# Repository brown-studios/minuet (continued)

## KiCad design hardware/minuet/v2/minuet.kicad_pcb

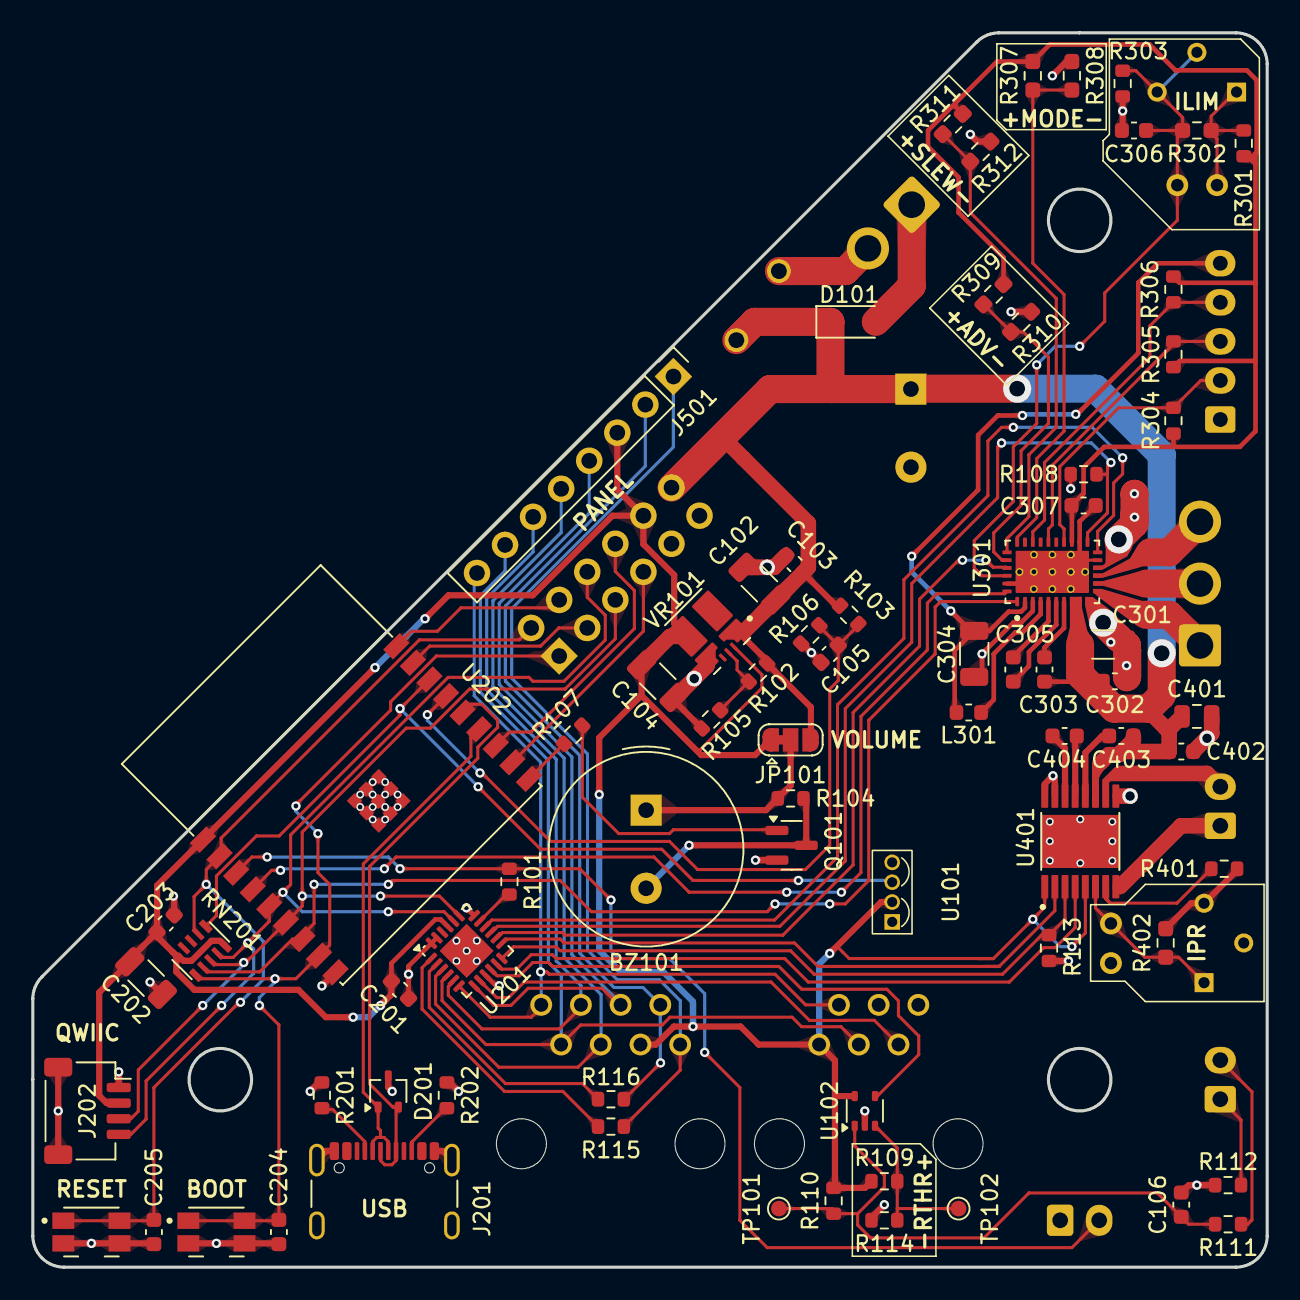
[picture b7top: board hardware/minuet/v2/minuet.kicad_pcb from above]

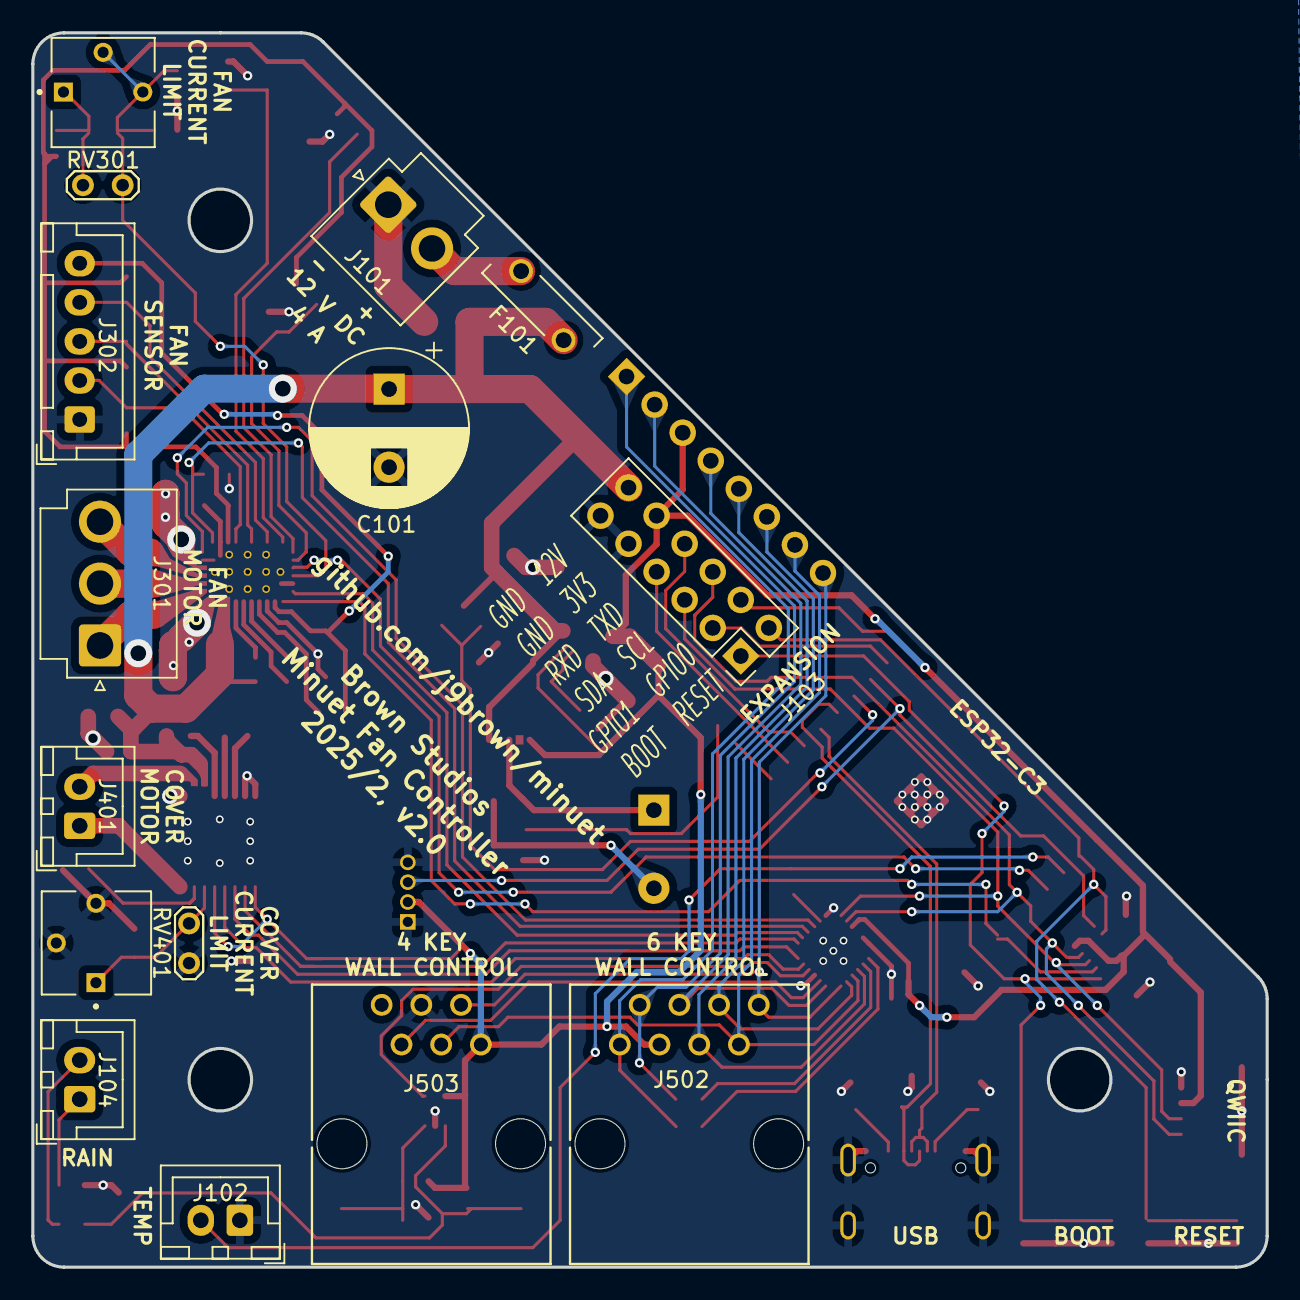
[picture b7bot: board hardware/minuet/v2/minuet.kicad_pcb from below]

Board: 2 copper layers, 79.0 x 79.0 mm, 93 parts (15 on the bottom side), 76 nets.

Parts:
BZ101: PS1240P02BT; Buzzer_TDK_PS1240P02BT_D12.2mm_H6.5mm
C101: 1000u; CP_Radial_D10.0mm_P5.00mm
C102, C202, C301: 10u; C_1206_3216Metric
C103, C106, C201, C203, C302, C306, C402, C403: 100n; C_0603_1608Metric
C104, C304: 22u; C_1206_3216Metric
C105, C205, C303, C307: 1u; C_0603_1608Metric
C204: 10p; C_0603_1608Metric
C305: 47n; C_0603_1608Metric
C401: 2.2u; C_0805_2012Metric
C404: 22n; C_0603_1608Metric
D101: SMF16A-E3-08; D_SMF
D201: DF3A5.6LFU; SOT-323_SC-70
F101: RGEF400K-2; RGEF400K
J101: B2P-VH-B; JST_VH_B2P-VH-B_1x02_P3.96mm_Vertical
J102, J104, J401: B2B-XH-A; JST_XH_B2B-XH-A_1x02_P2.50mm_Vertical
J103: PPPC062LFBN-RC; PinSocket_2x06_P2.54mm_Vertical
J201: USB4105-GF-A; USB_C_Receptacle_GCT_USB4105-xx-A_16P_TopMnt_Horizontal
J202: SM04B-SRSS-TB; JST_SH_SM04B-SRSS-TB_1x04-1MP_P1.00mm_Horizontal
J301: B3P-VH-B; JST_VH_B3P-VH-B_1x03_P3.96mm_Vertical
J302: B5B-XH-A; JST_XH_B5B-XH-A_1x05_P2.50mm_Vertical
J501: G800LE300018YEU; PinHeader_1x08_P2.54mm_Vertical
J502: MTJ-889X1; CONN_MTJ-889X1_ADM
J503: MTJ-669X1; CONN_MTJ-669X1_ADM
JP101: SolderJumper_3_Bridged12; SolderJumper-3_P1.3mm_Bridged12_RoundedPad1.0x1.5mm
L301: 22u; L_0603_1608Metric
NT101, NT401: NetTie_2; NetTie-2_SMD_Pad1.0mm
NT102, NT402: NetTie_2; NetTie-2_SMD_Pad0.2mm
Q101: MMBT3904; SOT-23
R101, R106, R107, R108, R113, R115, R116, R301, R303: 10K; R_0603_1608Metric
R102, R401: 62K; R_0603_1608Metric
R103, R109, R110, R111, R112: 100K; R_0603_1608Metric
R104: 1K; R_0603_1608Metric
R105: 22K; R_0603_1608Metric
R114: 1.5M; R_0603_1608Metric
R201, R202: 5.1K; R_0603_1608Metric
R302: 3.40K; R_0603_1608Metric_Pad0.98x0.95mm_HandSolder
R304, R305, R306: 4.7K; R_0603_1608Metric
R307, R309, R310, R311, R312: 0R; R_0603_1608Metric_Pad0.98x0.95mm_HandSolder
R308: 22K; R_0603_1608Metric_Pad0.98x0.95mm_HandSolder
R402: 2.80K; R_0603_1608Metric_Pad0.98x0.95mm_HandSolder
RN201: 746X101103JP; RESCAXS64P320X160X70-10N
RV301, RV401: 5K; TRIM_3362P-1-502LF
SW201, SW202: EVQ-P7A01P; SW_EVQ-P7A01P
TP101, TP102: TestPoint_Small; TestPoint_Pad_D1.0mm
TP301, TP401: TestPoint_2Pole; TestPoint_2Pads_Pitch2.54mm_Drill0.8mm
U101: TSOP39238; TSOP39238_Standoff
U102: LMV331X-SC5R; SOT-353_SC-70-5
U201: TCA9555RTWR; WQFN-24-1EP_4x4mm_P0.5mm_EP2.45x2.45mm
U202: ESP32-C3-WROOM-02
U301: MCT8315Z0HRRYR; IC_MCT8315Z0HRRYR
U401: DRV8876PWPR; IC_DRV8876PWPR
VR101: TPSM861253RDXR; VREG_TPSM861253RDXR

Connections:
+3.3V: C104.1, C201.1, C202.2, C203.1, J103.10, J202.2, J501.3, J502.3, J503.6, JP101.1 (A), NT102.2, NT402.1, R109.2, R110.1, RN201.5 (common), RN201.10 (common), U101.2 (Vs), U102.5 (V+), U201.21 (VCC), U202.1 (3V3), VR101.3 (VOUT)
+12V: C101.1, C301.1, C302.1, C303.1, D101.1 (A1), F101.2, J103.12, NT101.1, NT401.1, U301.8 (VM), U301.9 (VM)
/12V_IN: F101.1, J101.2
/12V_PWR: C102.1, C103.1, JP101.3 (B), NT101.2, R102.1, R103.2, VR101.1 (VIN)
/EN: R102.2, R105.1, VR101.6 (EN)
/RSEN: C106.1, R110.2, R111.2, TP101.1, U102.1 (+)
/RTHR: R109.1, R114.2, TP102.1, U102.3 (-)
/core/CC1: J201.A5 (CC1), R201.2
/core/CC2: J201.B5 (CC2), R202.1
/cover/CPH: C404.1, U401.13 (CPH)
/cover/CPL: C404.2, U401.14 (CPL)
/cover/IMODE: R401.2, U401.7 (IMODE)
/cover/IPROPI: R402.1, RV401.1, TP401.2, U401.6 (IPROPI)
/cover/OUT1: J401.1, U401.8 (OUT1)
/cover/OUT2: J401.2, U401.10 (OUT2)
/cover/VCP: C403.2, U401.12 (VCP)
/cover/VM: C401.2, C402.1, C403.1, NT401.2, U401.11 (VM)
/cover/VREF: NT402.2, U401.1 (EN/IN1), U401.5 (VREF)
/fan/ADVANCE: R309.2, R310.1, U301.28 (ADVANCE)
/fan/AVDD: C307.1, R301.1, R304.1, R305.1, R306.1, R307.1, R309.1, R311.1, U301.19 (AVDD)
/fan/ILIM: C306.1, R302.2, R303.1, RV301.2, RV301.3, TP301.1, U301.30 (ILIM)
/fan/MODE: R307.2, R308.1, U301.26 (MODE)
/fan/SLEW: R311.2, R312.1, U301.27 (SLEW)
/fan/U: J301.1, U301.11 (OUTA)
/fan/U_HALL: J302.2, R304.2, U301.20 (HPA)
/fan/V: J301.2, U301.12 (OUTB)
/fan/VBK: C304.1, J302.5, L301.1, U301.2 (FB_BK)
/fan/V_HALL: J302.3, R305.2, U301.22 (HPB)
/fan/W: J301.3, U301.13 (OUTC)
/fan/W_HALL: J302.4, R306.2, U301.24 (HPC)
/keypad/LED_AUTO: J501.1, J502.1, R115.2
/keypad/LED_RAIN: J501.2, J502.2, R116.2
BOOT: C204.1, J103.1, RN201.1 (R1), SW201.1_1, SW201.1_2, U202.8 (GPIO9)
GND: C101.2, C102.2, C103.2, C104.2, C105.2, C106.2, C201.2, C202.1, C203.2, C204.2, C205.2, C301.2, C302.2, C304.2, C306.2, C307.2, C401.1, C402.2, D101.2 (A2), D201.3 (A), J101.1, J102.1, J103.9, J103.11, J201.A1 (GND), J201.A12 (GND), J201.B1 (GND), J201.B12 (GND), J201.S1 (SHIELD), J202.1, J202.MP (MountPin), J302.1, J503.3, Q101.2 (E), R105.2, R106.1, R108.1, R112.2, R113.1, R114.1, R201.1, R202.2, R303.2, R308.2, R310.2, R312.2, R401.1, R402.2, RV401.2, RV401.3, SW201.2_1, SW201.2_2, SW202.2_1, SW202.2_2, TP401.1, U101.1 (GND), U101.4 (GND), U102.2 (V-), U201.9 (GND), U201.18 (A0), U201.23 (A1), U201.24 (A2), U201.25 (EPAD), U202.9 (GND), U202.19 (GND), U301.3 (GND_BK), U301.10 (PGND), U301.14 (PGND), U301.15 (DRVOFF), U301.18 (AGND), U301.31 (BRAKE), U301.33 (EP), U301.34 (EP), U301.35 (EP), U301.36 (EP), U301.37 (EP), U301.38 (EP), U301.39 (EP), U301.40 (EP), U301.41 (EP), U301.42 (EP), U301.43 (EP), U301.44 (EP), U401.9 (PGND), U401.15 (GND), U401.16 (PMODE), U401.17 (EXP), VR101.4 (PGND)
GPIO0: J103.4, U202.18 (GPIO0/ADC1_CH0/XTAL_32K_P)
GPIO1: J103.3, U202.17 (GPIO1/ADC1_CH1/XTAL_32K_N)
GPIO2_STRAP: RN201.6 (R5), U101.3 (OUT), U202.16 (GPIO2/ADC1_CH2)
GPIO3: C105.1, R103.1, R106.2, U202.15 (GPIO3/ADC1_CH3)
GPIO4: J102.2, R101.1, U202.3 (GPIO4/ADC1_CH4)
GPIO5: U202.4 (GPIO5/ADC2_CH0), U301.32 (PWM)
GPIO8_STRAP: RN201.2 (R2), U202.7 (GPIO8), U301.1 (FGOUT)
GPIO10: R107.2, U202.10 (GPIO10)
unnamed: BZ101.1 (+), JP101.2 (C), R104.1
unnamed: BZ101.2 (-), Q101.3 (C), R104.2
unnamed: J104.1, R112.1
unnamed: J104.2, R111.1
unnamed: Q101.1 (B), R107.1
unnamed: R301.2, R302.1, RV301.1, TP301.2
unnamed: C303.2, U301.7 (CP)
unnamed: C305.1, U301.6 (CPH)
unnamed: C305.2, U301.5 (CPL)
unnamed: L301.2, U301.4 (SW_BK)
unnamed: NT102.1, VR101.7 (VOS)
RESET: C205.1, J103.2, RN201.7 (R6), SW202.1_1, SW202.1_2, U202.2 (EN/CHIP_PU)
SCL: J103.6, J202.4, RN201.4 (R4), U201.20 (SDA), U202.5 (GPIO6)
SDA: J103.5, J202.3, RN201.3 (R3), U201.19 (SCL), U202.6 (GPIO7)
UART_RXD: J103.7, U202.11 (GPIO20/U0RXD)
UART_TXD: J103.8, U202.12 (GPIO21/U0TXD)
USB_D+: D201.2 (K), J201.A6 (D+), J201.B6 (D+), U202.14 (GPIO19/USB_D+)
USB_D-: D201.1 (K), J201.A7 (D-), J201.B7 (D-), U202.13 (GPIO18/USB_D-)
XIO0: R115.1, U201.1 (P00)
XIO1: R116.1, U201.2 (P01)
XIO2: J501.5, J502.5, U201.3 (P02)
XIO3: J501.7, J502.7, J503.4, U201.4 (P03)
XIO4: J501.6, J502.6, U201.5 (P04)
XIO5: J501.8, J502.8, J503.5, U201.6 (P05)
XIO6: J501.4, J502.4, U201.7 (P06)
XIO7: J503.2, U201.8 (P07)
XIO8: U102.4, U201.10
XIO9: U201.11, U401.4 (~NFAULT)
XIO10: R113.2, U201.12, U401.3 (NSLEEP)
XIO11: U201.13, U401.2 (PH/IN2)
XIO12: U201.14, U301.29 (DIR)
XIO13: R108.2, U201.15, U301.17 (~SLEEP)
XIO14: U201.16, U301.16 (~FAULT)
XIO15: R101.2, U201.17

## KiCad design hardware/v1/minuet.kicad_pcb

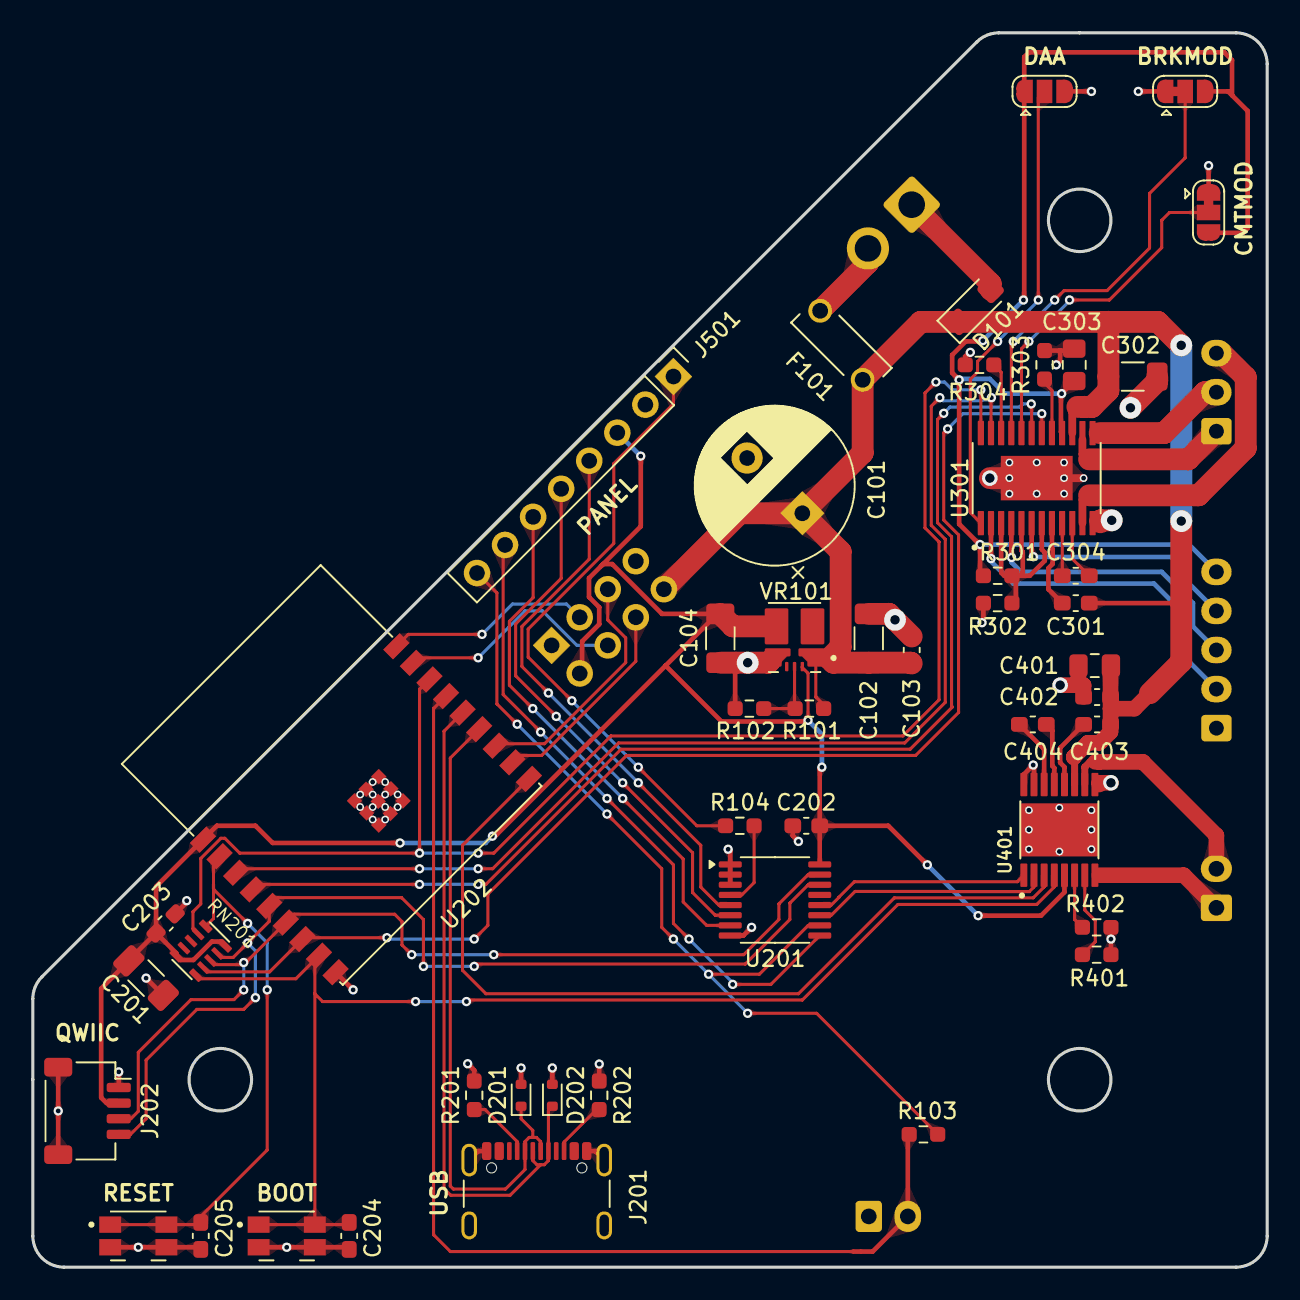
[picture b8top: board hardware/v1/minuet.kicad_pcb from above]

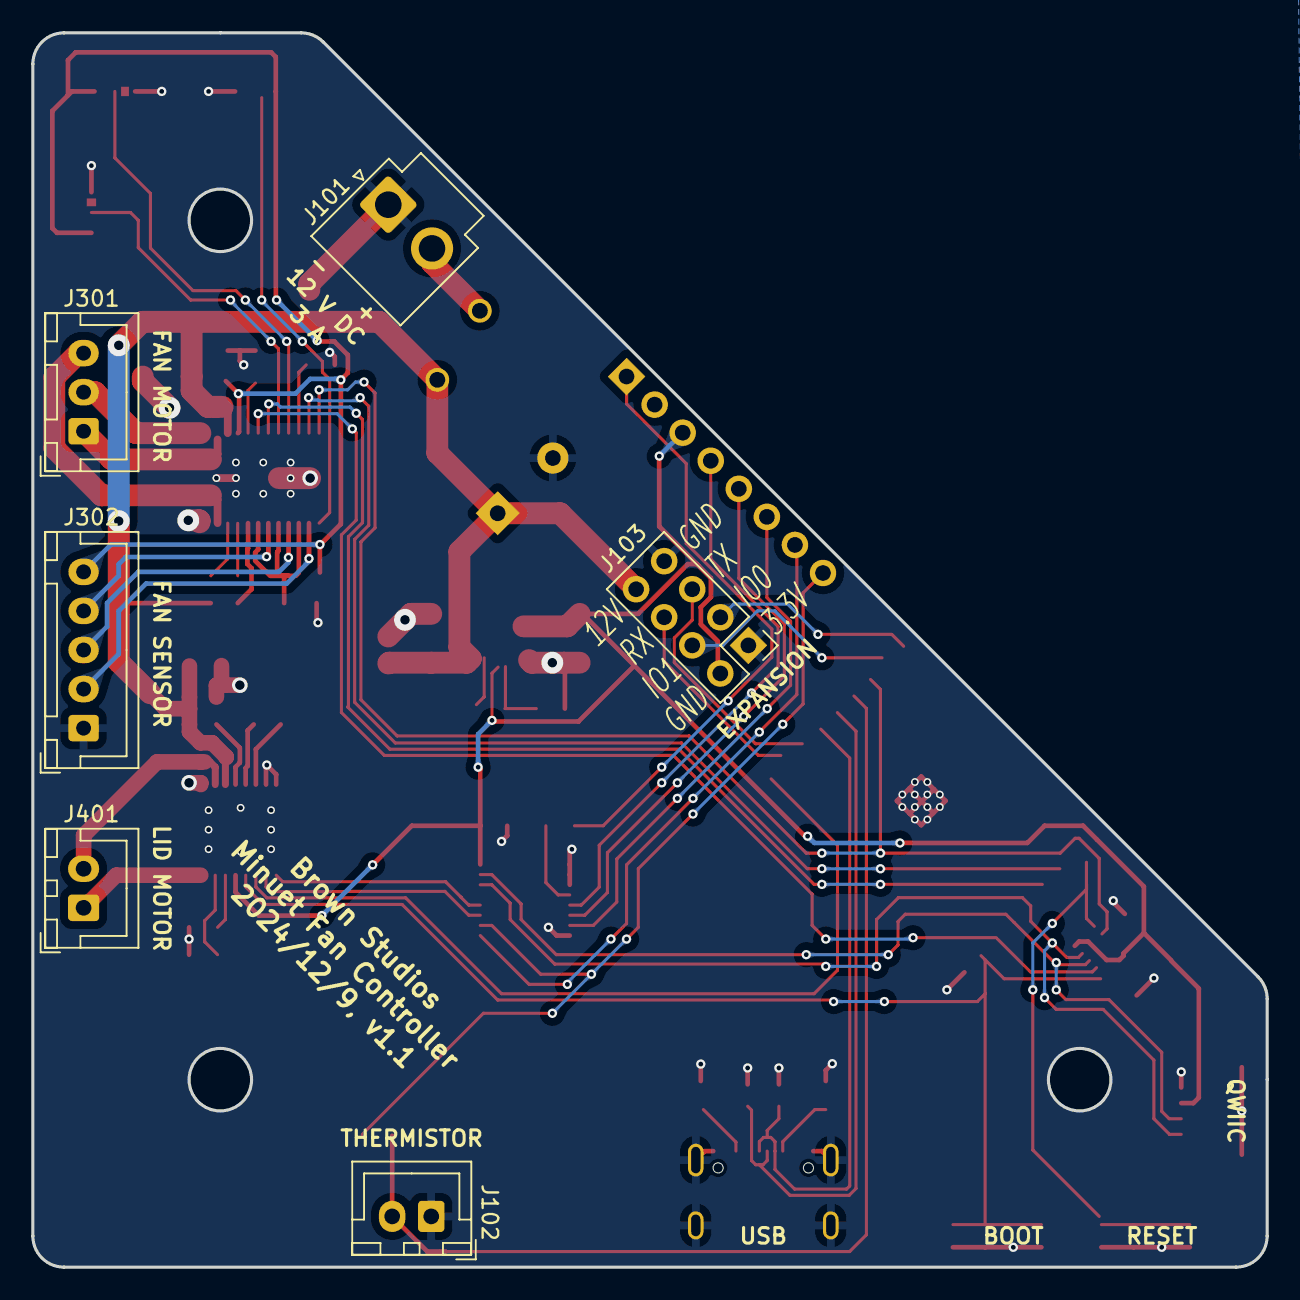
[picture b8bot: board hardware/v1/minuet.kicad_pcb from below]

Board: 2 copper layers, 79.0 x 79.0 mm, 55 parts (6 on the bottom side), 57 nets.

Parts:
C101: 680u; CP_Radial_D10.0mm_P5.00mm
C102, C201, C302: 10u; C_1206_3216Metric_Pad1.33x1.80mm_HandSolder
C103, C202, C203, C304, C402, C403: 100n; C_0603_1608Metric_Pad1.08x0.95mm_HandSolder
C104: 22u; C_1206_3216Metric_Pad1.33x1.80mm_HandSolder
C204: 10p; C_0603_1608Metric_Pad1.08x0.95mm_HandSolder
C205, C301: 1u; C_0603_1608Metric_Pad1.08x0.95mm_HandSolder
C303, C401: 2.2u; C_0805_2012Metric_Pad1.18x1.45mm_HandSolder
C404: 22n; C_0603_1608Metric_Pad1.08x0.95mm_HandSolder
D101: SMF16A-E3-08; D_SMF
D201, D202: TPD1E10B06DYAR; D_SOD-523
F101: RGEF300K-2; FUSRR505W81L660T250H1360
J101: VH_B2P-VH-B; JST_VH_B2P-VH-B_1x02_P3.96mm_Vertical
J102: B2B-XH-A_1; JST_XH_B2B-XH-A_1x02_P2.50mm_Vertical
J103: Conn_02x04; PinHeader_2x04_P2.54mm_Vertical
J201: USB4105-GF-A; USB_C_Receptacle_GCT_USB4105-xx-A_16P_TopMnt_Horizontal
J202: SM04B-SRSS-TB; JST_SH_SM04B-SRSS-TB_1x04-1MP_P1.00mm_Horizontal
J301: B3B-XH-A; JST_XH_B3B-XH-A_1x03_P2.50mm_Vertical
J302: B5B-XH-A; JST_XH_B5B-XH-A_1x05_P2.50mm_Vertical
J401: B2B-XH-A; JST_XH_B2B-XH-A_1x02_P2.50mm_Vertical
J501: Header; PinHeader_1x08_P2.54mm_Vertical
JP301, JP303: SolderJumper_3_Bridged12; SolderJumper-3_P1.3mm_Bridged12_RoundedPad1.0x1.5mm
JP302: SolderJumper_3_Open; SolderJumper-3_P1.3mm_Open_RoundedPad1.0x1.5mm
NT101: NetTie_2; NetTie-2_SMD_Pad0.3mm
NT401: NetTie_2; NetTie-2_SMD_Pad1.0mm
R101, R401: 62K; R_0603_1608Metric_Pad0.98x0.95mm_HandSolder
R102, R303: 22K; R_0603_1608Metric_Pad0.98x0.95mm_HandSolder
R103, R104, R301, R302, R304: 10K; R_0603_1608Metric_Pad0.98x0.95mm_HandSolder
R201, R202: 5.1K; R_0603_1608Metric_Pad0.98x0.95mm_HandSolder
R402: 6.8K; R_0603_1608Metric_Pad0.98x0.95mm_HandSolder
RN201: 746X101103JP; RESCAXS64P320X160X70-10N
SW201, SW202: EVQ-P7A01P; SW_EVQ-P7A01P
U201: TCA9554PWR; TSSOP-16_4.4x5mm_P0.65mm
U202: ESP32-C3-WROOM-02
U301: DRV10970PWP; SOP65P640X120-25N
U401: DRV8876PWPR; IC_DRV8876PWPR
VR101: TPSM861253RDXR; VREG_TPSM861253RDXR

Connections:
+3.3V: C104.1, C201.2, C202.1, C203.2, J103.2, J202.2, J501.3, RN201.5 (common), RN201.10 (common), U201.16 (VDD), U202.1 (3V3), U401.5 (VREF), VR101.3 (VOUT), VR101.7 (VOS)
+12V: C101.1, C102.1, C103.1, C301.2, C302.1, D101.1 (A1), F101.2, J103.8, NT401.1, R101.1, U301.15 (VM), VR101.1 (VIN)
/12V_IN: F101.1, J101.2
/EN: R101.2, R102.1, VR101.6 (EN)
/TH: J102.2, NT101.2, R103.1
/core/CC1: J201.A5 (CC1), R201.2
/core/CC2: J201.B5 (CC2), R202.1
/fan/BRKMOD: JP301.2 (C), U301.21 (BRKMOD)
/fan/CMTMOD: JP303.2 (C), U301.20 (CMTMOD)
/fan/CPN: C304.2, U301.10 (CPN)
/fan/CPP: C304.1, U301.9 (CPP)
/fan/CS: R303.2, U301.17 (CS)
/fan/DAA: JP302.2 (C), U301.1 (DAA)
/fan/RETRY: R304.2, U301.22 (RETRY)
/fan/U: J301.1, U301.14 (U)
/fan/U_HALL: J302.2, U301.2 (U_HP)
/fan/V: J301.2, U301.13 (V)
/fan/VCP: C301.1, U301.8 (VCP)
/fan/VINT: C303.2, J302.5, JP301.3 (B), JP302.1 (A), JP303.3 (B), R301.1, U301.16 (VINT)
/fan/VINT/2: R301.2, R302.1, U301.3 (U_HN), U301.5 (V_HN), U301.7 (W_HN)
/fan/V_HALL: J302.3, U301.4 (V_HP)
/fan/W: J301.3, U301.11 (W)
/fan/W_HALL: J302.4, U301.6 (W_HP)
/keypad/LED_AUTO: J501.1, R104.2
/lid/CPH: C404.1, U401.13 (CPH)
/lid/CPL: C404.2, U401.14 (CPL)
/lid/IMODE: R401.2, U401.7 (IMODE)
/lid/IPROPI: R402.2, U401.6 (IPROPI)
/lid/OUT1: J401.1, U401.8 (OUT1)
/lid/OUT2: J401.2, U401.10 (OUT2)
/lid/VCP: C403.2, U401.12 (VCP)
/lid/VM: C401.2, C402.1, C403.1, NT401.2, U401.11 (VM)
CHIP_EN: C205.1, RN201.6 (R5), SW202.1_1, SW202.1_2, U202.2 (EN/CHIP_PU)
GND: C101.2, C102.2, C103.2, C104.2, C201.1, C202.2, C203.1, C204.2, C205.2, C302.2, C303.1, C401.1, C402.2, D101.2 (A2), D201.2 (A2), D202.2 (A2), J101.1, J102.1, J103.1, J103.7, J201.A1 (GND), J201.A12 (GND), J201.B1 (GND), J201.B12 (GND), J201.S1 (SHIELD), J202.1, J202.MP (MountPin), J302.1, JP301.1 (A), JP302.3 (B), JP303.1 (A), R102.2, R201.1, R202.2, R302.2, R303.1, R304.1, R401.1, R402.1, SW201.2_1, SW201.2_2, SW202.2_1, SW202.2_2, U201.1 (A0), U201.2 (A1), U201.3 (A2), U201.8 (GND), U202.9 (GND), U202.19 (GND), U301.12 (GND), U301.25 (PAD), U401.9 (PGND), U401.15 (GND), U401.16 (PMODE), U401.17 (EXP), VR101.4 (PGND)
IO0: J103.3, U202.18 (GPIO0/ADC1_CH0/XTAL_32K_P)
IO1: J103.4, U202.17 (GPIO1/ADC1_CH1/XTAL_32K_N)
IO2_STRAP: RN201.7 (R6), U202.16 (GPIO2/ADC1_CH2), U301.24 (FG)
IO3: NT101.1, U202.15 (GPIO3/ADC1_CH3)
IO4: U202.3 (GPIO4/ADC1_CH4), U301.23 (FR)
IO5: U202.4 (GPIO5/ADC2_CH0), U301.19 (PWM)
IO8_STRAP: RN201.2 (R2), U202.7 (GPIO8), U301.18 (RD)
IO9_STRAP: C204.1, RN201.1 (R1), SW201.1_1, SW201.1_2, U202.8 (GPIO9), U401.4 (~NFAULT)
IO10: U202.10 (GPIO10), U401.3 (NSLEEP)
SCL: J202.4, RN201.4 (R4), U201.14 (SCL), U202.5 (GPIO6)
SDA: J202.3, RN201.3 (R3), U201.15 (SDA), U202.6 (GPIO7)
UART_RXD: J103.6, U202.11 (GPIO20/U0RXD)
UART_TXD: J103.5, U202.12 (GPIO21/U0TXD)
USB_D+: D202.1 (A1), J201.A6 (D+), J201.B6 (D+), U202.14 (GPIO19/USB_D+)
USB_D-: D201.1 (A1), J201.A7 (D-), J201.B7 (D-), U202.13 (GPIO18/USB_D-)
XIO0: R104.1, U201.4 (P0)
XIO1: J501.4, U201.5 (P1)
XIO2: J501.5, U201.6 (P2)
XIO3: J501.6, U201.7 (P3)
XIO4: J501.7, U201.9 (P4)
XIO5: J501.8, R103.2, U201.10 (P5)
XIO6: U201.11 (P6), U401.2 (PH/IN2)
XIO7: U201.12 (P7), U401.1 (EN/IN1)

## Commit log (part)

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2024-12-30 Add CERN-OHL-W license
2025-01-09 Add the documentation and ESPHome configuration.
2025-01-09 Add v1 hardware.
2025-01-09 Mention the antenna
2025-01-09 Add license notice.
2025-01-10 Update comment to match actual behavior
2025-02-05 Work in progress on Minuet revision 2.
    This new revision uses a higher current BLDC driver for the fan motor
    and adds many features that were omitted from the initial prototype.
2025-02-08 Complete draft of the v2 PCB
2025-02-09 Create an accessory for driving lighting and other loads.
    Plugs into the Minuet v2 extension port.
2025-02-09 Prepare Minuet v2 for fabrication.
2025-02-09 Move Minuet main board to a subdirectory.
2025-02-09 Add documentation links for the lighting and load accessory.
2025-02-09 Wordsmithing accessories and components.
2025-02-09 Finishing touches for v2
2025-02-09 Finishing touches for v2.
2025-02-10 Update project status
2025-02-17 Update license notice
2025-02-20 Make the piezo buzzer symbol unpolarized.
2025-02-20 Update software and documentation for v2.
    Update all components to use the new I/O pins.
    Add IR receiver, piezo buzzer, wall control, rain sensor.
    Implement IR protocol parsing.
    Reorganize the YAML file by component.
    Update the motor docs with the v2 motor phase order.
    Rename the top-level configurations for clarity.
2025-02-20 Simplify protocol bit debug code.
2025-02-20 Update for v2.
2025-02-20 Retrieve the Maxxfan protocol from an external component.
    The code was moved to https://github.com/j9brown/esphome-maxxfan-protocol
2025-02-20 Remove the Maxxfan Deluxe qualification from the introduction.
    Minuet should work with some Maxxfan Plus models too.
2025-02-20 Add packages for the light accessory.
2025-02-20 Acknowledge wingspinner's contributions to the IR protocol.
2025-02-20 Abandon load accessory design, update errata.
    Decided to abandon this design because it is overly complex and
    doesn't work with addressable LEDs as intended. It would be better
    to design simpler boards for each use-case instead of having lots
    of jumpers.
2025-02-20 More clearly call out the supported hardware version.
2025-02-21 Add new light accessory.
    Connects a dimmable LED or addressable LED strip to the fan.
    This design supersedes the prior lighting and load accessory and has
    been simplified for just this purpose.
2025-02-21 Update documentation to refer to the light accessory.
2025-02-24 Link to the esphome-maxxfan-project.
2025-02-24 Say a little more about what v1 was about.
2025-02-24 Finalize light accessory v2.5 for manufacture.
2025-02-24 Finalize Minuet v2.1 for manufacture.
    This revision uses a different motor controller and buck converter
    and remedies errata from v2.0.
2025-02-24 Replace maximum current with available current
2025-02-24 Update pins for Minuet v2.1.
2025-03-08 Replace the flicker effect with fireworks
2025-03-10 Update Minuet v2.2 ILIM resistor setting.
    The default current limits are just a little too low, fix that in
    the next revision. Also improved the documentation with markdown tables
    for each setting.
2025-03-10 Update docs for Minuet v2.1.
2025-03-10 Ignore private local files.
2025-03-10 Redesign the control scheme and document it.
    Add an option to toggle between "standard" and "enhanced" controls
    which mainly changes how the automatic thermostat is configured
    using the keypad. The keypad behavior with the enhanced controls is
    modeless so the buttons always do the same thing regardless of whether
    the thermostat is on. The thermostat can be overridden just by pressing
    a button to change the state of the fan and then it can be re-engaged
2025-03-10 Relabel intake/exhaust using the phases air in/out.
2025-03-10 Increase motor PWM frequency and make it configurable for testing.
    Anything above about 20 KHz should render the switching noise inaudible
    to most people and higher frequencies incur greater switching losses.
    Set it to 24 KHz somewhat arbitrarily as that corresponds to the Nyquist
    frequency of CD quality audio recordings. Noted the difference with
    a spectrometer.
2025-03-10 Turn off motors and lights on shutdown.
    They'll be turned off when the hardware reinitializes after
    a reboot but it's better to be safe just in case.
2025-03-10 Support brushed fan motors on the MCT8316Z.
    This is a bit of a hack because it requires resetting the motor lock
    timeout periodically but it's enough to compare the behavior of the
    motors. The SPI variant of this chip allows the lock timeout to be
    disabled. Too bad it isn't I2C as that would be easier to work with.
    For the factory motor, connect the white wire to motor phase U and
    the black wire to motor phase V with a JST VH-3 connector. Also
2025-03-10 Ensure cover change reverts operation in progress.
2025-03-14 Ensure duty cycle converges to zero
2025-04-11 Add support for controlling the light accessory from the keypad.
2025-04-11 Switch to the ESP-IDF framework.
2025-04-14 Amend errata for v2.1.
2025-04-14 Add a configuration file for a kit including the light accessory
2025-04-14 Ignore esphome build files
2025-04-14 Provide audible feedback for actions with unseen effects
2025-04-14 Update the motor duty cycle table for the 50 W motor.
    This table should perhaps be replaced with some kind of speed control
    loop based on the tachometer reading.
2025-04-14 Improve lighting transitions.
    Disabled gamma correction for the addressable LED strips to workaround a
    problem with the fade in from off to on essentially doing nothing for
    the majority of the transition then jumping to the final state.
    See: https://github.com/esphome/issues/issues/2397
2025-04-14 Don't override auto fan control when direction changes and is same as manual
2025-04-14 Raise the arbitrary speed used for auto fan control.
    Still need to implement a control loop that accounts for temperature
    differences and human comfort.
2025-04-14 Set the wifi switch default to off for captive portals.
    Improves security when the user hasn't configured any credentials.
2025-04-21 Add a setting to override the fan duty cycle for testing purposes.
2025-04-21 Delay changing cover motor direction to prevent early stalls.
2025-04-22 Add a switch to control the thermostat override.
2025-04-22 Snapshot both fan and cover on manual override.
    Ensures that the manually overridden state is preserved when the
    thermostat is disabled.
2025-04-28 Calibrate the color of the LED strip, approximately.
2025-05-19 Duplicate v2 to begin work on v3.
2025-05-22 Fix documentation links.
2025-05-22 First draft of Minuet v3.
2025-05-22 Document Minuet v2 as obsolete; it is superseded by v3.
2025-05-23 Prepare for fabrication.
2025-05-23 Move light accessory to v2.
2025-05-23 Update hardware status in documentation
2025-05-23 Amend errata
2025-05-23 Remove unnecessary fields.
2025-05-23 Create v3 of light accessory for redesigned expansion port.
2025-06-05 Add a connector for input controls.
2025-06-06 Add support for 24 key infrared light remote.
    Improved color calibration and effects.
2025-06-06 Finalize light accessory for fabrication.
2025-06-06 Add tooling holes and PCBA offsets.
2025-07-04 Increase PWM frequency to 1kHz from 400 Hz to reduce flickering
2025-07-04 Prepare light accessory v3 for production
2025-07-04 Prepare Minuet v3 for production.
2025-07-10 Don't auto-reboot when the API connection is lost.
    The fan should always be capable of operating standalone.
2025-07-10 Disable serial port log output to improve performance
2025-07-10 Emphasize dressing the wires to prevent damage during installation
2025-07-10 Improve auto and light controls.
    Add documentation on using a 24-key RGBW LED IR remote.
    Support changing the brightness of the light.
    Hold auto to reset the temperature setpoint in both modes.
    Fix a bug that would improperly exit auto when releasing a combo.
2025-07-11 Update the project development progress.
2025-07-11 Rewrite the logic for persisting fan state.
    Ensure that the state is restored correctly after a restart including
    whether the manual override has been engaged.
    The fan always turns off when the thermostat is disabled.
2025-07-11 Publish initial state for rain sensor
2025-08-12 Replace deprecated uses of publish_initial_state.
2025-08-19 Update firmware for Minuet v3, integrate MCF8316D chip
2025-08-20 Fix sensor delta filters.
2025-08-20 Make the rain sensor a little more responsive to dry conditions.
2025-08-20 Add a diagnostic switch to engage the fan motor brake input.
    Useful for testing purposes. It has uncovered a possible conflict
    between the brake function and the watchdog timer that results in a
    WATCHDOG_FAULT being reported when braking.
2025-08-20 Handle motor driver sleep/wake behavior and faults.
    Allows time for transient faults to resolve themselves before stopping
    the motor..
2025-08-20 Add to v3 errata
2025-08-20 Revert to ESP-IDF 5.3.2 to workaround I2C errors in 5.4.2.
2025-08-21 Implement failsafe restarts.
2025-08-21 Refactor fan driver code to shorten the identifiers a bit.
2025-08-21 Use recommended ESP-IDF version.
    MCF8316 component now has a workaround for the compatibility issue.
2025-08-21 Improve speed control and fault tolerance.
2025-08-23 Implement the safety lock feature.
2025-08-23 Implement a simple automatic fan speed algorithm.
    Also added a few more thermostat presets.
2025-08-25 Use include vars for hardware compatibility.
    Updated core.yaml to support Minuet v3.0 and v3.1 pin differences.
    Updated light accessories to support various LED strips.
    Added errata and workaround regarding GPIO6 pin initial state in v3.0.
2025-08-25 Update repository location
2025-08-25 Add step files for making assembly fixtures
2025-08-29 Move firmware to minuet-firmware repository.
2025-08-29 Improve documentation of safety lock and wifi switch
2025-08-29 Add standoff model height to errata.
2025-08-29 Remove superseded hardware designs.
    They will remain in the git history for posterity.
2025-09-11 Update and reorganize the documentation for Minuet v3.
2025-09-12 Add direct links to each PCB design near the top of the hardware guide
2025-09-19 Add docs for fan motor health monitoring.
2025-09-19 Amend hardware setup
2025-09-22 The lid motor cable needs to be a little longer.
2025-09-22 Add a more informative table of compatible hardware.
    Amend errata with the limitations of the current end-of-travel detection
    method for the lid motor.
2025-09-22 Add a wire passage cover model and improved the installation instructions.
    Also updated the link for the fan motor mount model.
2025-09-22 Fix the JST VH connector housing designation for the motor
2025-09-24 Add a link to the video about installing the LED strip.
2025-09-27 Add an errata about unexpected restarts in WiFi AP mode.
2025-09-28 Clarify the type of screw to use for the motor mount adapter.
2025-10-05 Add a Home Assistant dashboard example including YAML.
2025-10-06 Add documentation for new features.
    Enhanced controls are now the default.
    Can set the thermostat fan/lid mode as a combinated function.
    Can suppress keypad indicators.
    Added a quick reference table for the controls right at the start.
2025-10-26 Migrate light project to KiCad 9 for v4.
2025-10-26 Migrate minuet project to KiCad 9 for v4.
2026-02-25 Wordsmithing and link to firmware repo.
2026-02-25 Update errata.
2026-02-25 Update project for KiCad 9.
2026-04-04 First draft of Minuet v4 fan controller board
2026-04-10 Second draft of Minuet v4 main board.
2026-04-10 First draft of Minuet light accessory v4.
2026-04-13 Add DNP footprint for CT slew rate capacitor.
2026-04-13 Move IR receiver to center on aperture
2026-04-20 Design environment sensor.
2026-04-20 Prepare light accessory for fabrication
2026-04-21 Prepare main board for fabrication
